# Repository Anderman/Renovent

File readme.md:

# Renovent 

## Installatie Screenshot

## Web interface

## homeassistant

# software documentatie
De originele controller is een display met toetsen en 1 IC
De IC zet een 3 bit counter om in 8 select lijnen van het display.

Display is een  [liteon](https://eu.mouser.com/datasheet/3/281/1/LTC_4627JS.pdf)
De 8 segementen worden in volgorde aan gestuurd met een freq van 500uS
Welke segmenten verlicht worden gaat met digit 1 - 4

Het programma zal dus het continue het display moeten uitlezen en wat er op staat omzetten in een 4 char array.
Hiervan met gebruik gemaakt worden van mapping om een 8 bit array om te zetten in een Char. Waarschijnlijk kan de DP los en hebben we een 7 bitarray naar char mapping nodig.

De switches werken als volgt

Er is 1 output Key_node.
sw1 (OK) = key_node=1 als C=1 (counter=1)
Sw2 (+ ) = key_node=1 als D=1 (counter=5)
Sw3 (F ) = key_node=1 als E=1 (counter=6)
Sw4 (- ) = key_node=1 als DP=1 (counter=3)

## ESP32 aansluiting

In het ESP32-schema worden de relevante signalen van de originele controller eerst via een SN74LVC245 naar 3V3 gebracht. De ESP32 ziet dus alleen de 3V3-varianten van deze signalen.

### Ingangen voor het uitlezen van display en toetsen

- BIT0 -> BIT0_3V3 -> GPIO35
- BIT1 -> BIT1_3V3 -> GPIO36
- BIT2 -> BIT2_3V3 -> GPIO37
- Digit1 -> Digit1_3V3 -> GPIO38
- Digit2 -> Digit2_3V3 -> GPIO39
- Digit3 -> Digit3_3V3 -> GPIO40
- Digit4 -> Digit4_3V3 -> GPIO41
- KEY_NODE -> KEY_NODE_3V3 -> GPIO42

Deze acht ingangen zijn voldoende om het gemultiplexte display en de toetsstatus te reconstrueren.

### Uitgang voor toets simulatie

- KEY_DOWN <- GPIO43

KEY_DOWN gaat via een BSS138-transistor naar de originele schakeling. Daarmee kan de ESP32 een toetsdruk simuleren zonder direct 5V op een GPIO te zetten.

### Overige aansluitingen op het ESP32-bord

- SDA_1 -> GPIO7
- SCL_1 -> GPIO8
- LED -> GPIO12

## Aanpak in software

De displaycontroller loopt elke 500 us door de 8 segment-selects. De software leest dus niet "digit 1", daarna "digit 2", enzovoort, maar leest per segment-select in een keer de toestand van alle 4 digitlijnen.

Concreet:

1. `BIT0`, `BIT1` en `BIT2` vormen samen een tellerwaarde van `0..7`.
2. Die tellerwaarde bepaalt welk segment op dat moment actief is.
3. Tegelijk wordt gekeken welke van `Digit1..Digit4` hoog zijn.
4. Voor het actieve segment wordt dat bit gezet in alle digits die op dat moment hoog zijn.
5. Na 8 select-stappen is er een compleet 4-digit frame opgebouwd.

De mapping van de tellerwaarde naar segment is:

| BIT2 BIT1 BIT0 | index | segment |
| --- | --- | --- |
| 0 0 0 | 0 | A |
| 0 0 1 | 1 | C |
| 0 1 0 | 2 | B |
| 0 1 1 | 3 | DP |
| 1 0 0 | 4 | F |
| 1 0 1 | 5 | D |
| 1 1 0 | 6 | E |
| 1 1 1 | 7 | G |

Schematisch ziet een volledige scan er zo uit:

```mermaid
flowchart LR
	A[GPIO snapshot] --> B[Lees BIT0..2]
	B --> C[Select-index 0..7]
	C --> D[Segment voor deze stap kiezen]
	D --> E{Lees Digit1..4 in dezelfde snapshot}
	E --> F[Zet dit ene segment in digit 1..4 als die hoog zijn]
	F --> G[Werk lopend frame bij]
	G --> H{Zijn alle 8 select-stappen gezien?}
	H -- nee --> A
	H -- ja --> I[4 complete digitmasks klaar]
	I --> J[Zet digitmasks om naar displaytekst]
```

Eén interrupt-snapshot doet dus niet alles. Per snapshot gebeurt maar dit:

- bepaal welk segment nu actief is via `BIT0..2`
- lees tegelijk welke van de 4 digitlijnen actief zijn
- zet dat ene segment in de digits die op dat moment hoog zijn

Pas nadat dit 8 keer gebeurd is, hebben we voor alle 4 digits een volledig segmentmasker.

Je kunt het ook zo lezen: we lezen niet "4 displays na elkaar", maar per segment in een keer alle 4 displays.

Voorbeeld:

- `BIT2..0 = 000` betekent segment `A`
- als op dat moment `Digit1` en `Digit3` hoog zijn, dan krijgt digit 1 en digit 3 het segment `A`
- bij de volgende select-stap wordt bijvoorbeeld segment `C` op dezelfde manier verdeeld over de 4 digits
- na alle 8 segmenten kennen we van elke digit het volledige segmentmasker

`KEY_NODE` wordt in diezelfde scan meegelezen. Een actieve key tijdens een specifieke select-index betekent een specifieke toets.

## Interrupt of polling

De huidige implementatie gebruikt juist een interrupt op `BIT0`.

Waarom:

- de select-bits veranderen snel genoeg dat polling onnodig veel jitter gaf
- de reader wil alle relevante lijnen op exact hetzelfde moment samplen
- daarom leest de ISR direct een volledige GPIO-snapshot en reconstrueert daaruit de actuele select-index, digitlijnen en `KEY_NODE`

De implementatie in `src/display_reader.cpp` werkt zo:

1. `BIT0` triggert `onBit0ChangeInterrupt()` op elke flank.
2. De ISR leest direct `GPIO.in1.val`, zodat alle ingangssignalen uit hetzelfde tijdsmoment komen.
3. Uit `BIT0..2` wordt de verwachte select-index bepaald.
4. Als een select-stap ontbreekt of de volgorde niet klopt, wordt het huidige frame weggegooid.
5. Na select `7` is een volledig frame klaar.
6. De hoofdloop publiceert pas een frame als twee opeenvolgende complete frames gelijk zijn.

Daardoor is de reader robuuster tegen timingglitches en worden half-opgebouwde displaybeelden niet gepubliceerd.

## Huidige softwarebasis

Er is nu een eerste ESP32 software-opzet toegevoegd in de map `src`.

- `src/main.cpp` start WiFi, de webserver en de display reader.
- `src/wifiSetup.*` gebruikt WiFiManager, net als in het andere project.
- `src/display_reader.*` leest BIT0..2, Digit1..4 en KEY_NODE in en bouwt daar een stabiel displayframe van op.
- `src/webui/webui.*` publiceert een simpele HTTP API en serveert statische bestanden uit SPIFFS.
- `data/index.html` is een eenvoudige debugpagina.

### Webinterface

Na boot:

- hoofd-UI op poort 80
- WiFiManager portal op poort 8080

Beschikbare endpoints:

- `GET /api/status`
- `POST /api/keydown`

`/api/status` geeft onder andere terug:

- gedecodeerde displaytekst
- actieve toets op basis van `KEY_NODE`
- WiFi-status

### PlatformIO

Er is ook een `partitions/default.csv` toegevoegd zodat de SPIFFS data-partitie beschikbaar is voor de webpagina.

Voor lokaal gebruik zijn deze commando's relevant:

1. `platformio run`
2. `platformio run --target buildfs`
3. `platformio run --target uploadfs`
4. `platformio run --target upload`

### OTA artifacts lokaal bouwen

De automatische firmware-update leest OTA-bestanden uit `release/firmware`, `release/spiffs` en `release/latest.json`.

Deze artifacts worden lokaal gegenereerd door `scripts/generate_build_info.py`, dat als PlatformIO build hook meeloopt. De hook:

- berekent een aparte hash voor `src` en `data`
- bewaart per component precies een markerbestand `*.hash` in `src` en `ui-hashes`
- schrijft alleen een nieuwe build-id als de hash van die component gewijzigd is
- kopieert de nieuwe `.bin` naar `release/firmware` of `release/spiffs`
- werkt daarna `release/latest.json` bij

Voor een volledige lokale OTA release bouw je beide artifacts:

1. `platformio run -e esp32s3mini_ota`
2. `platformio run -e esp32s3mini_ota -t buildfs`

Daarna kun je de bijgewerkte bestanden in `release/` zelf committen of op een andere manier publiceren, zolang `release/latest.json` en de bijbehorende `.bin` bestanden bereikbaar blijven voor de ESP32.

### Backtrace decoderen

Een ESP32-S3 backtrace uit de WebUI of seriele output kun je direct tegen de actuele firmware-ELF symboliseren met:

```powershell
.\scripts\decode_backtrace.ps1 "0x4037EF71 -> 0x40377C96 -> 0x40376AEF"
```

Het script gebruikt standaard:

- `.pio/build/esp32s3mini_ota/firmware.elf`
- de PlatformIO `xtensa-esp32s3-elf-addr2line.exe`

Belangrijk: decode altijd tegen de ELF van dezelfde firmware-build als waarmee de crash is ontstaan, anders kloppen functies en regelnummers mogelijk niet.

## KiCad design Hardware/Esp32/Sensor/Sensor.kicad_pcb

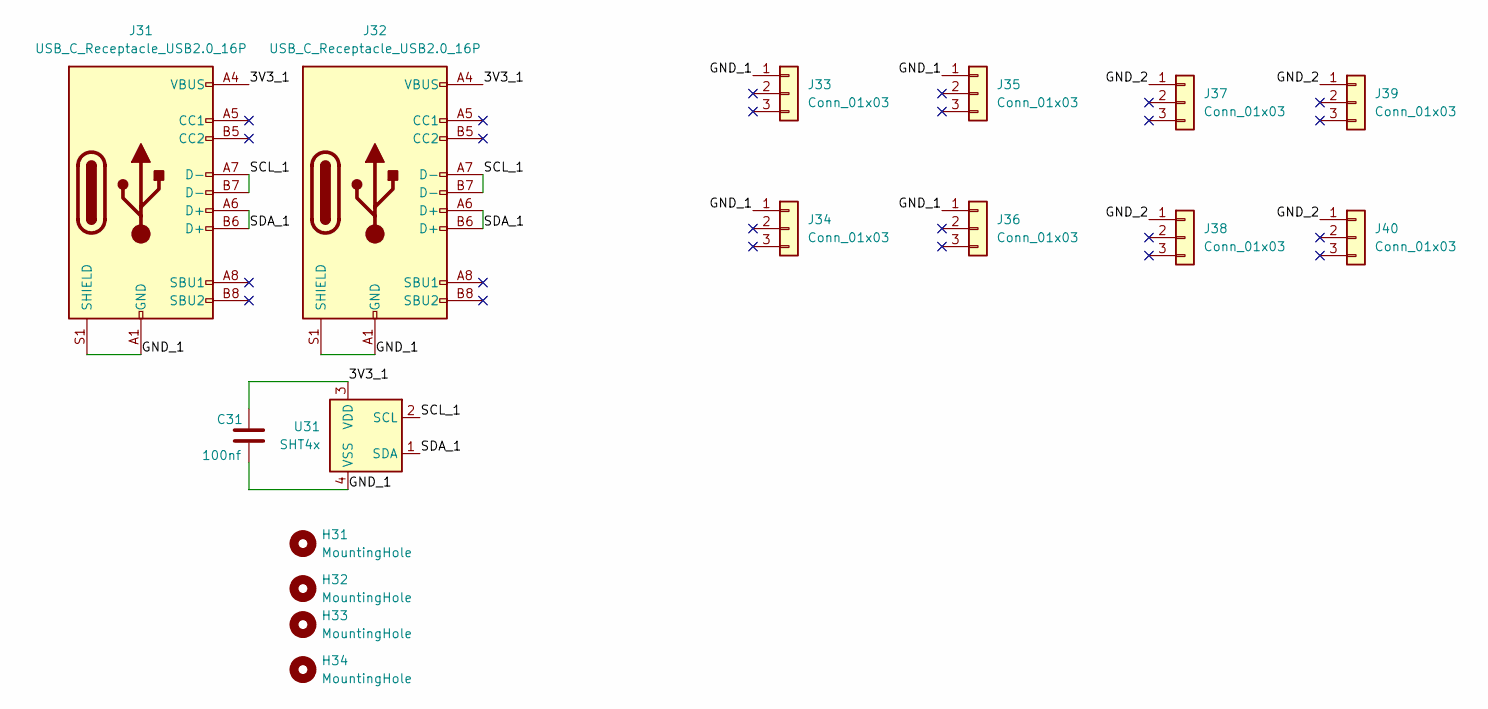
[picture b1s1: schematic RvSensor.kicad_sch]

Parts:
C31: 100nf; C_0402_1005Metric; LCSC C1525
H31, H32, H33, H34: MountingHole; MountingHole_2.5mm
J31, J32: USB_C_Receptacle_USB2.0_16P; USB_C_Receptacle_HRO_TYPE-C-31-M-12; LCSC C36936538
J33, J34, J35, J36: Conn_01x03; PinSocket_1x03_P2.00mm_Vertical_female_C2935967; LCSC C2935967
J37, J38, J39, J40: Conn_01x03; PinHeader_1x03_P2.00mm_Vertical_male_C541857; LCSC C541857
U31: SHT4x; Sensirion_DFN-4_1.5x1.5mm_P0.8mm_SHT4x_NoCentralPad; LCSC C7461852

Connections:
/RvSensor/3V3_1: C31.1, J31.A4 (VBUS), J31.A9 (VBUS), J31.B4 (VBUS), J31.B9 (VBUS), J32.A4 (VBUS), J32.A9 (VBUS), J32.B4 (VBUS), J32.B9 (VBUS), U31.3 (VDD)
/RvSensor/GND_1: C31.2, J31.A1 (GND), J31.A12 (GND), J31.B1 (GND), J31.B12 (GND), J31.S1 (SHIELD), J32.A1 (GND), J32.A12 (GND), J32.B1 (GND), J32.B12 (GND), J32.S1 (SHIELD), J33.1, J34.1, J35.1, J36.1, U31.4 (VSS)
/RvSensor/GND_2: J37.1, J38.1, J39.1, J40.1
/RvSensor/SCL_1: J31.A7 (D-), J31.B7 (D-), J32.A7 (D-), J32.B7 (D-), U31.2 (SCL)
/RvSensor/SDA_1: J31.A6 (D+), J31.B6 (D+), J32.A6 (D+), J32.B6 (D+), U31.1 (SDA)

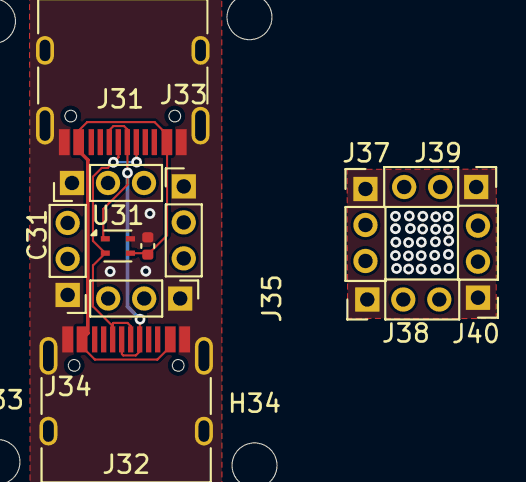
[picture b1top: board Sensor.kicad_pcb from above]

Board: 2 copper layers, 16 parts (0 on the bottom side), 5 nets.

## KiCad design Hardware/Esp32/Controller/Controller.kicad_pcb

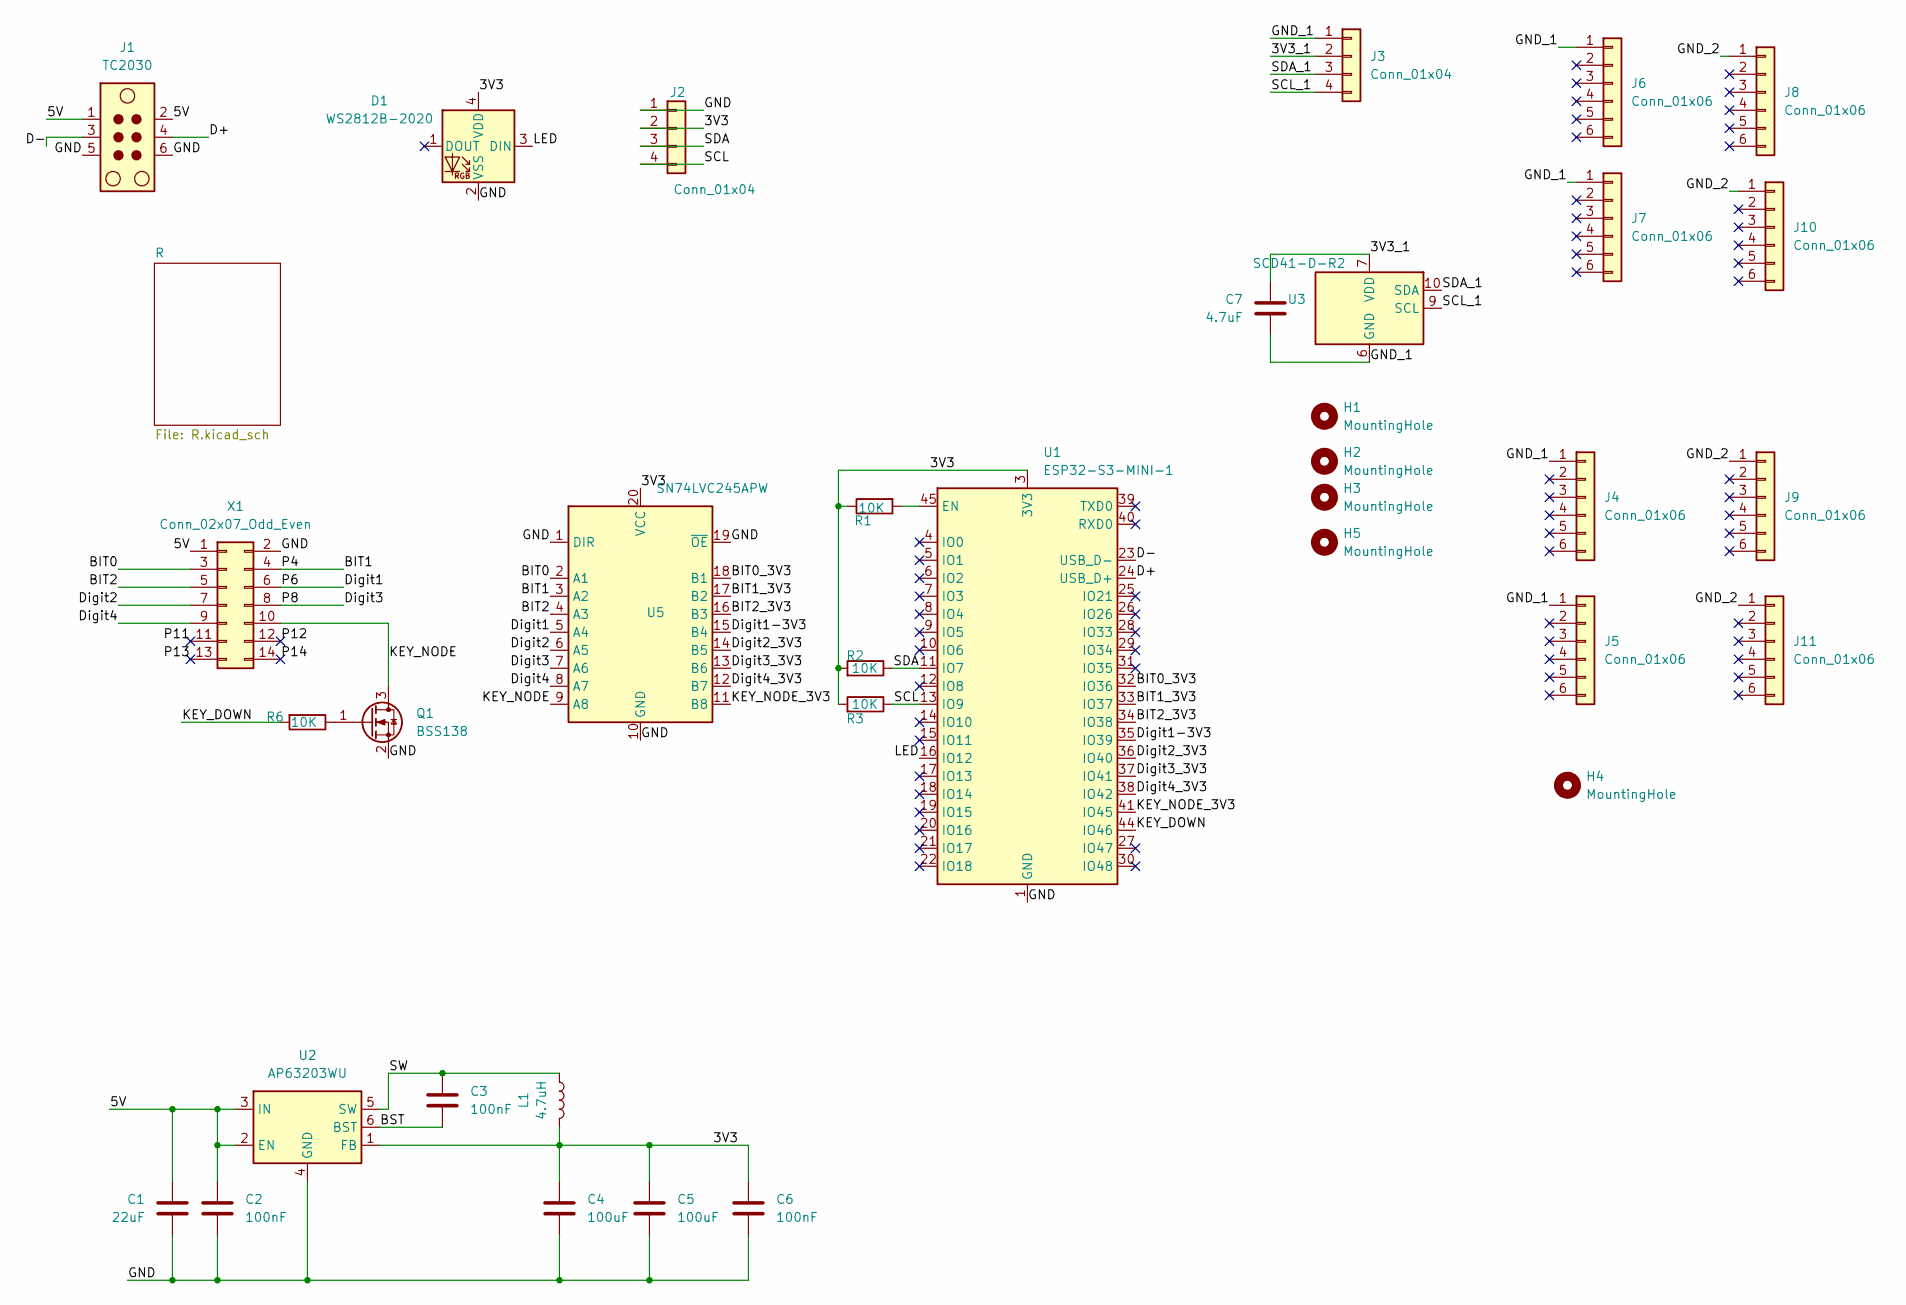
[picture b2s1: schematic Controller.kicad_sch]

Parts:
C1: 22uF; C_0805_2012Metric; LCSC C5674
C2, C3: 100nF; C_0603_1608Metric; LCSC C56476
C4, C5: 100uF; C_1206_3216Metric; LCSC C15008
C6: 100nF; C_0201_0603Metric; LCSC C76934
C7: 4.7uF; C_0603_1608Metric; LCSC C19666
D1: WS2812B-2020; LED_WS2812B-2020_2x2.2mm; LCSC C965555
H1, H2, H3, H5: MountingHole; MountingHole_2.5mm
H4: MountingHole; MountingHole_7mm
J1: TC2030; Tag-Connect_TC2030-IDC-NL_2x03_P1.27mm_Vertical
J2, J3: Conn_01x04; JST_PH_S4B-PH-SM4-TB_1x04-1MP_P2.00mm_Horizontal; LCSC C157926
J4, J5, J6, J7: Conn_01x06; PinSocket_1x06_P2.00mm_Vertical_female_C7499363; LCSC C7499363
J8, J9, J10, J11: Conn_01x06; PinHeader_1x06_P2.00mm_Vertical_male_C706993; LCSC C706993
L1: 4.7uH; L_Bourns-SRN4018; LCSC C5159668
Q1: BSS138; SOT-23; LCSC C20917
R1, R2, R3, R6: 10K; R_0402_1005Metric; LCSC C25744
U1: ESP32-S3-MINI-1; LCSC C3013941
U2: AP63203WU; TSOT-23-6; LCSC C780769
U3: SCD41-D-R2; Sensirion_SCD4x-1EP_10.1x10.1mm_P1.25mm_EP4.8x4.8mm; LCSC C3659294
U5: SN74LVC245APW; TSSOP-20_4.4x6.5mm_P0.65mm; LCSC C45384750
X1: Conn_02x07_Odd_Even; IDC-Header_2x07_P2.54mm_Vertical; LCSC C9037

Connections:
/3V3: C4.1, C5.1, C6.1, D1.4 (VDD), J2.2, L1.2, R1.1, R2.2, R3.2, U1.3 (3V3), U2.1 (FB), U5.20 (VCC)
/3V3_1: C7.1, J3.2, U3.7 (VDD), U3.19 (VDD)
/5V: C1.1, C2.1, J1.1, J1.2, U2.2 (EN), U2.3 (IN), X1.1
/BIT0: U5.2 (A1), X1.3
/BIT0_3V3: U1.32 (IO36), U5.18 (B1)
/BIT1: U5.3 (A2), X1.4
/BIT1_3V3: U1.33 (IO37), U5.17 (B2)
/BIT2: U5.4 (A3), X1.5
/BIT2_3V3: U1.34 (IO38), U5.16 (B3)
/BST: C3.2, U2.6 (BST)
/D+: J1.4, U1.24 (USB_D+)
/D-: J1.3, U1.23 (USB_D-)
/Digit1: U5.5 (A4), X1.6
/Digit1-3V3: U1.35 (IO39), U5.15 (B4)
/Digit2: U5.6 (A5), X1.7
/Digit2_3V3: U1.36 (IO40), U5.14 (B5)
/Digit3: U5.7 (A6), X1.8
/Digit3_3V3: U1.37 (IO41), U5.13 (B6)
/Digit4: U5.8 (A7), X1.9
/Digit4_3V3: U1.38 (IO42), U5.12 (B7)
/GND: C1.2, C2.2, C4.2, C5.2, C6.2, D1.2 (VSS), J1.5, J1.6, J2.1, Q1.2 (S), U1.1 (GND), U1.2 (GND), U1.42 (GND), U1.43 (GND), U1.46 (GND), U1.47 (GND), U1.48 (GND), U1.49 (GND), U1.50 (GND), U1.51 (GND), U1.52 (GND), U1.53 (GND), U1.54 (GND), U1.55 (GND), U1.56 (GND), U1.57 (GND), U1.58 (GND), U1.59 (GND), U1.60 (GND), U1.61 (GND), U1.62 (GND), U1.63 (GND), U1.64 (GND), U1.65 (GND), U2.4 (GND), U5.1 (DIR), U5.10 (GND), U5.19 (~OE), X1.2
/GND_1: C7.2, J3.1, J4.1, J5.1, J6.1, J7.1, U3.6 (GND), U3.20 (GND), U3.21 (GND)
/GND_2: J8.1, J9.1, J10.1, J11.1
/KEY_DOWN: R6.2, U1.44 (IO46)
/KEY_NODE: Q1.3 (D), U5.9 (A8), X1.10
/KEY_NODE_3V3: U1.41 (IO45), U5.11 (B8)
/LED: D1.3 (DIN), U1.16 (IO12)
/P11: X1.11
/P12: X1.12
/P13: X1.13
/P14: X1.14
/SCL: J2.4, R3.1, U1.13 (IO9)
/SCL_1: J3.4, U3.9 (SCL)
/SDA: J2.3, R2.1, U1.11 (IO7)
/SDA_1: J3.3, U3.10 (SDA)
/SW: C3.1, L1.1, U2.5 (SW)
unnamed: Q1.1 (G), R6.1
unnamed: R1.2, U1.45 (EN)

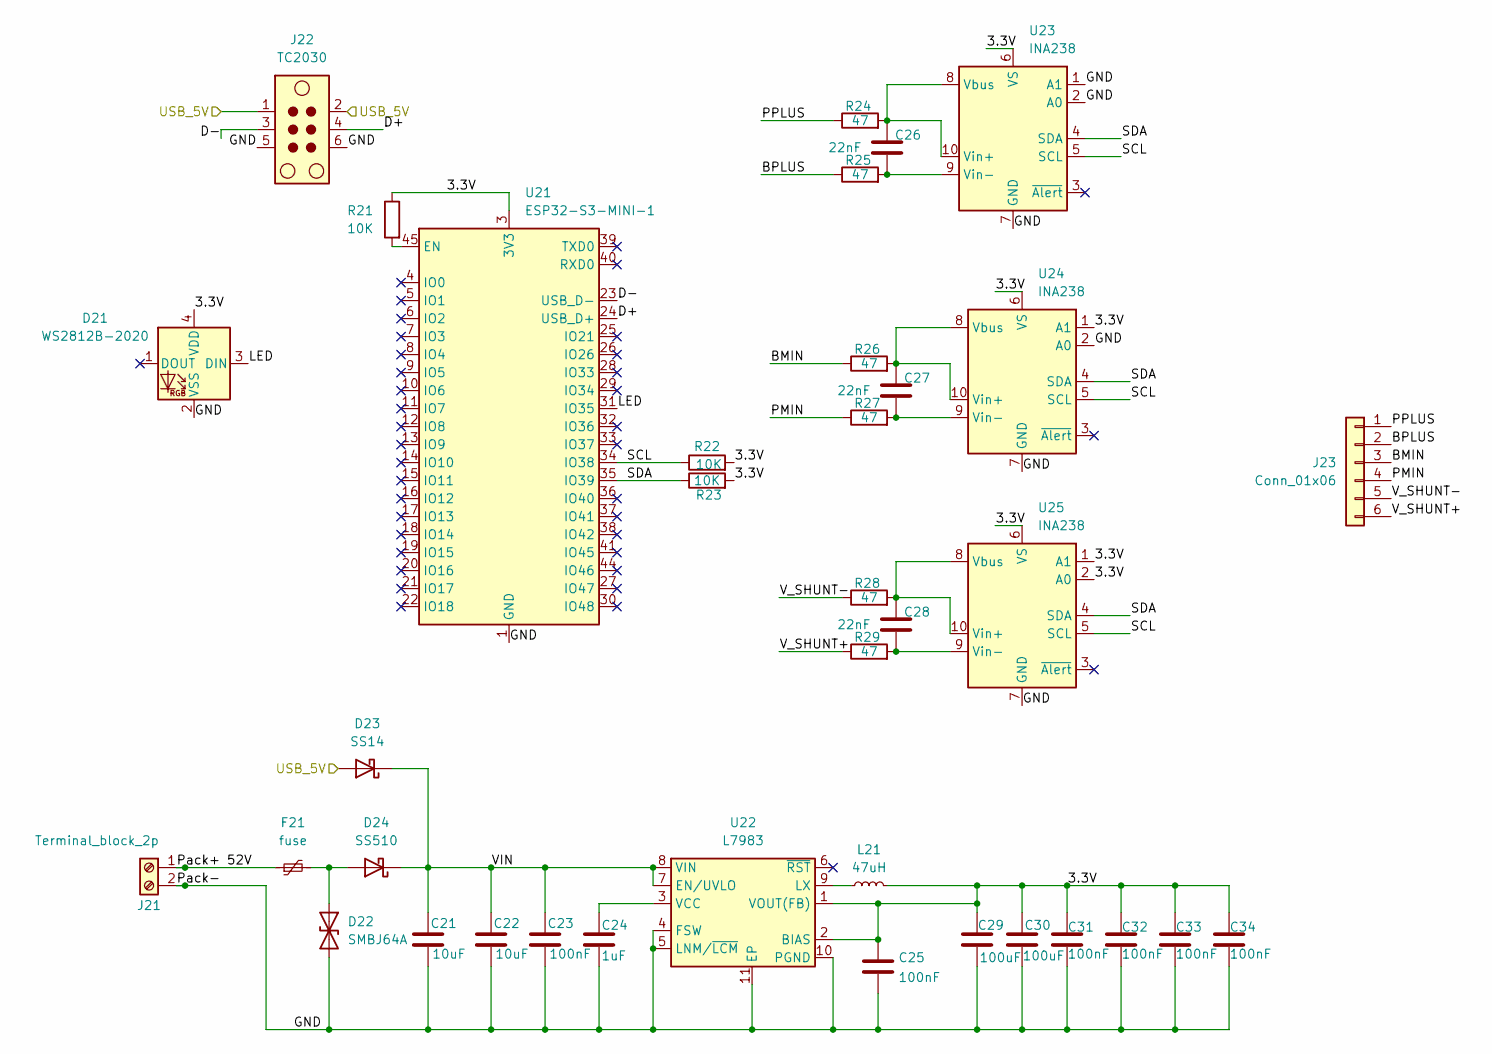
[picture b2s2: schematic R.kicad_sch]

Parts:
C21, C22: 10uF; C_1210_3225Metric; LCSC C576517
C23: 100nF; C_0402_1005Metric; LCSC C162178
C24: 1uF; C_0603_1608Metric; LCSC C23829972
C25, C31, C32, C33, C34: 100nF; C_0201_0603Metric; LCSC C76934
C26, C27, C28: 22nF; C_0603_1608Metric; LCSC C161234
C29, C30: 100uF; C_1206_3216Metric; LCSC C15008
D21: WS2812B-2020; LED_WS2812B-2020_2x2.2mm; LCSC C965555
D22: SMBJ64A; D_SMB; LCSC C19077594
D23: SS14; D_SMA; LCSC C2480
D24: SS510; D_SMA; LCSC C18199171
F21: fuse; Fuse_1812_4532Metric; LCSC C2830263
J21: Terminal_block_2p; TerminalBlock_Phoenix_MKDS-1-2-3.81_1x02_P3.81mm_Horizontal; LCSC C5188452
J22: TC2030; Tag-Connect_TC2030-IDC-NL_2x03_P1.27mm_Vertical
J23: Conn_01x06; JST_PH_S6B-PH-SM4-TB_1x06-1MP_P2.00mm_Horizontal; LCSC C265405
L21: 47uH; L_APV_ANR5040; LCSC C167974
R21: 10K; R_0402_1005Metric; LCSC C25744
R22, R23: 10K; R_0603_1608Metric; LCSC C25804
R24, R25, R26, R27, R28, R29: 47; R_0603_1608Metric; LCSC C23182
U21: ESP32-S3-MINI-1; LCSC C3013941
U22: L7983; TDFN-10-1EP_3x3mm_P0.5mm; LCSC C1518764
U23, U24, U25: INA238; VSSOP-10_3x3mm_P0.5mm; LCSC C2868250

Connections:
/R/3.3V: C25.1, C29.1, C30.1, C31.1, C32.1, C33.1, C34.1, D21.4 (VDD), L21.2, R21.1, R22.2, R23.2, U21.3 (3V3), U22.1 (VOUT(FB)), U22.2 (BIAS), U23.6 (VS), U24.1 (A1), U24.6 (VS), U25.1 (A1), U25.2 (A0), U25.6 (VS)
/R/BMIN: J23.3, R26.1
/R/BPLUS: J23.2, R25.1
/R/D+: J22.4, U21.24 (USB_D+)
/R/D-: J22.3, U21.23 (USB_D-)
/R/GND: C21.2, C22.2, C23.2, C24.2, C25.2, C29.2, C30.2, C31.2, C32.2, C33.2, C34.2, D21.2 (VSS), D22.2 (A2), J21.2, J22.5, J22.6, U21.1 (GND), U21.2 (GND), U21.42 (GND), U21.43 (GND), U21.46 (GND), U21.47 (GND), U21.48 (GND), U21.49 (GND), U21.50 (GND), U21.51 (GND), U21.52 (GND), U21.53 (GND), U21.54 (GND), U21.55 (GND), U21.56 (GND), U21.57 (GND), U21.58 (GND), U21.59 (GND), U21.60 (GND), U21.61 (GND), U21.62 (GND), U21.63 (GND), U21.64 (GND), U21.65 (GND), U22.4 (FSW), U22.5 (LNM/~LCM), U22.10 (PGND), U22.11 (EP), U23.1 (A1), U23.2 (A0), U23.7 (GND), U24.2 (A0), U24.7 (GND), U25.7 (GND)
/R/LED: D21.3 (DIN), U21.31 (IO35)
/R/PMIN: J23.4, R27.1
/R/PPLUS: J23.1, R24.1
/R/Pack+ 52V: F21.1, J21.1
/R/SCL: R22.1, U21.34 (IO38), U23.5 (SCL), U24.5 (SCL), U25.5 (SCL)
/R/SDA: R23.1, U21.35 (IO39), U23.4 (SDA), U24.4 (SDA), U25.4 (SDA)
/R/USB_5V: D23.2 (A), J22.1, J22.2
/R/VIN: C21.1, C22.1, C23.1, D23.1 (K), D24.1 (K), U22.7 (EN/UVLO), U22.8 (VIN)
/R/V_SHUNT+: J23.6, R29.1
/R/V_SHUNT-: J23.5, R28.1
unnamed: D22.1 (A1), D24.2 (A), F21.2
unnamed: R21.2, U21.45 (EN)
unnamed: L21.1, U22.9 (LX)
unnamed: C24.1, U22.3 (VCC)
unnamed: C26.1, R24.2, U23.8 (Vbus), U23.10 (Vin+)
unnamed: C26.2, R25.2, U23.9 (Vin-)
unnamed: C27.1, R26.2, U24.8 (Vbus), U24.10 (Vin+)
unnamed: C27.2, R27.2, U24.9 (Vin-)
unnamed: C28.1, R28.2, U25.8 (Vbus), U25.10 (Vin+)
unnamed: C28.2, R29.2, U25.9 (Vin-)

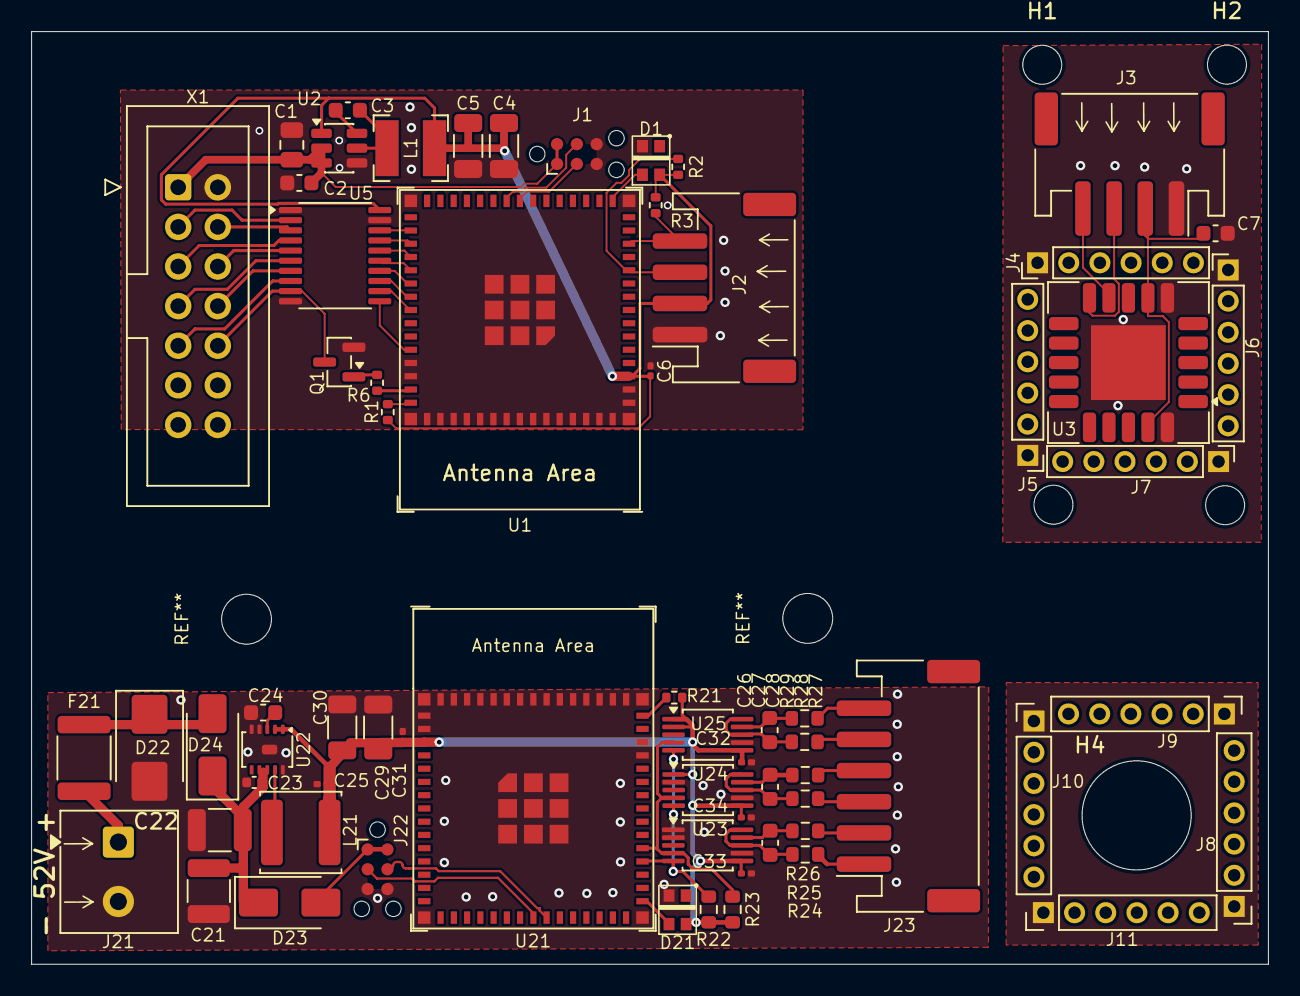
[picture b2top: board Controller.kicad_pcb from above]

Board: 2 copper layers, 79.3 x 59.8 mm, 72 parts (0 on the bottom side), 60 nets.

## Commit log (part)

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2026-04-06 Working version. With reading / writing values
2026-04-06 Refactor tasks and enhance key handling logic
    - Updated task arguments in tasks.json for better readability.
    - Enabled auto scan for sensors in app_config.h.
    - Updated build ID in build_info.generated.h.
    - Added auto-release functionality in key_writer.cpp.
    - Introduced pulseKeys function in key_writer.h for key press duration control.
    - Improved sensors menu logic to handle startup scan state.
2026-04-06 Implement MQTT configuration management and enhance reset info handling
2026-04-07 Add MQTT discovery functionality and entity definitions
    - Introduced ha_entity_definitions.h to define entity structures and enums for Home Assistant integration.
    - Implemented mqtt_discovery.cpp to handle MQTT connection, message processing, and state publishing for various entities.
    - Created mqtt_discovery.h for function declarations related to MQTT discovery setup and loop.
    - Added mqtt_discovery_payload.cpp and mqtt_discovery_payload.h to manage the construction of discovery payloads using ArduinoJson.
    - Enhanced command handling for settings and ventilation modes, including queuing and processing commands.
    - Implemented functions to publish CO2 sensor data, settings, and sensor menu st
2026-05-03 update hardware
2026-05-03 Add Huminty abs, Backtrace, push 4s io 3s
2026-05-03 fix autoupate
2026-05-03 Publish OTA artifacts 20260503T140010Z
2026-05-03 Publish OTA artifacts 20260503T141106Z
2026-05-03 Publish OTA artifacts 20260503T144306Z [skip ci]
2026-05-03 refactor OTA update logic to use manifest URL
2026-05-03 Publish OTA artifacts 20260503T150701Z [skip ci]
2026-05-03 cleanup logging auto update
2026-05-03 Publish OTA artifacts 20260503T153635Z [skip ci]
2026-05-03 Publish OTA artifacts 20260503T154819Z [skip ci]
2026-05-03 Publish OTA artifacts 20260503T155817Z [skip ci]
2026-05-03 Publish OTA artifacts 20260503T172719Z [skip ci]
2026-05-03 Publish OTA artifacts 20260503T175601Z [skip ci]
2026-05-04 Fix spikes on co2 sensor when reset/reboot
2026-05-04 cleanup display reader
2026-05-04 Update readme met mermaid flow
2026-05-04 Cleanup keywriter
2026-05-04 connect to strongest AP , cleanup key_writer
2026-05-04 Fxi unknown entries in sensor menu, cleanup mqtt
2026-05-05 cleanup mtqq
2026-05-05 fix setting writer
2026-05-05 Add Optie print docs
2026-05-05 fix sensor reader
2026-05-05 fix spiffs
2026-05-09 fix write settings cleanup mqtt code
2026-05-09 fix ha change setting. Do not set old values before finish update. Add Optionprint sensors
2026-05-09 Fix increase timeout on write settings. Fix hang in write setting on out of range values
2026-05-09 cleanup setting-writer
2026-05-09 write setting to menu fix negatief and letters
2026-05-10 create subfolders
2026-05-10 remove display logging
2026-05-10 cleanup menu readers fix outofRange values
2026-05-10 cleanup sensor menu and setting writer
2026-05-10 Force update HA, add logger
2026-05-10 fix ui
